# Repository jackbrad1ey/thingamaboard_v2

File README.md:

# Thingamaboard V2
This is the second iteration of my custom mechanical keyboard, a low-profile board aiming to be reliable, portable and fully-featured.

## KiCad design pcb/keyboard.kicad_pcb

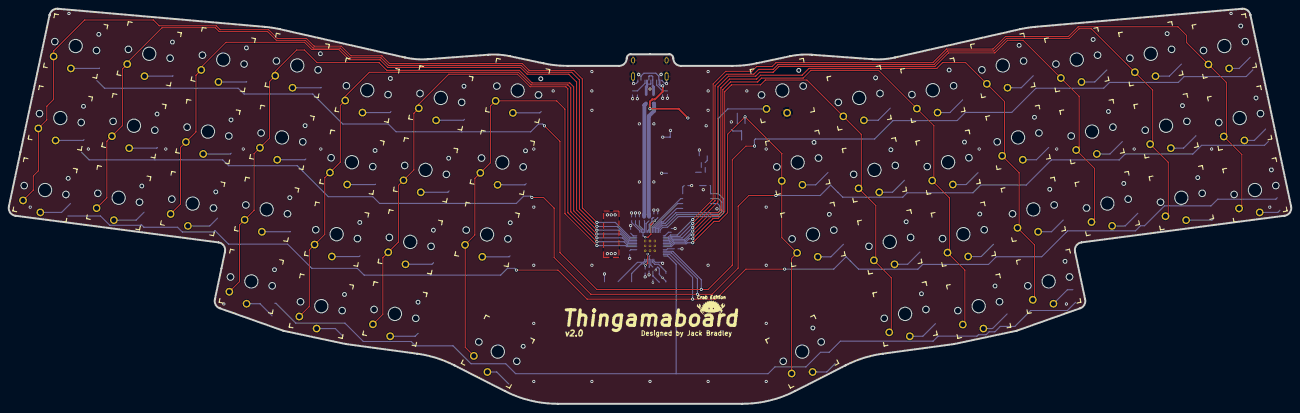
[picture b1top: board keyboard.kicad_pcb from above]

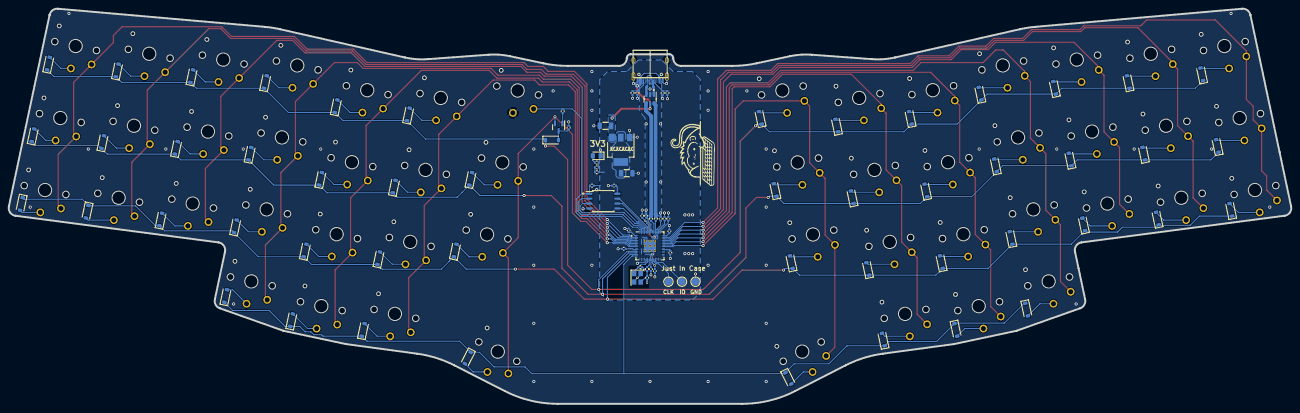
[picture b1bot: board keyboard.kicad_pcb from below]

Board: 2 copper layers, 331.1 x 102.0 mm, 140 parts (90 on the bottom side), 95 nets.

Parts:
C1, C16: 10u; C_1206_3216Metric
C2, C5, C6, C7, C10, C11, C12, C13, C14, C15: 100n; C_0402_1005Metric
C3, C4: 15p; C_0402_1005Metric
C8, C9: 1u; C_0402_1005Metric
D1: NCD0805; LED_0805_2012Metric_Pad1.15x1.40mm_HandSolder
D2, D3, D4, D5, D6, D7, D8, D9, D10, D11, D12, D13, D14, D15, D16, D17, D18, D19, D20, D21, D22, D23, D24, D25, D26, D27, D28, D29, D30, D31, D32, D33, D34, D35, D36, D37, D38, D39, D40, D41, D42, D43, D44, D45, D46, D47, D48, D49, D50, D51: D_Small; D_SOD-123
J1: USB_C_Receptacle_USB2.0; TYPE-C-31-M-12
Q1: S8550; SOT-23
R1, R2, R3, R12, R13: 27; R_0402_1005Metric
R4, R5, R6, R7, R8, R10: 10k; R_0402_1005Metric
R9, R11: 1k; R_0402_1005Metric
SW1, SW2, SW3, SW4, SW5, SW6, SW7, SW8, SW9, SW10, SW11, SW12, SW13, SW14, SW15, SW16, SW17, SW18, SW19, SW20, SW21, SW22, SW23, SW24, SW25, SW26, SW27, SW28, SW29, SW30, SW31, SW32, SW33, SW34, SW35, SW36, SW37, SW38, SW39, SW40, SW41, SW42, SW43, SW44, SW45, SW46, SW47, SW48, SW49, SW50: SW_Push; SW_PG1350
TP1, TP2, TP3: TestPoint; TestPoint_Pad_D2.0mm
U1: NCP1117-3.3_SOT223; SOT-223-3_TabPin2
U2: USBLC6-2SC6; SOT-23-6
U3: W25Q128JVS; SOIC-8_5.23x5.23mm_P1.27mm
U4: RP2040; QFN-56-1EP_7x7mm_P0.4mm_EP3.2x3.2mm
Y1: ABM8-272_T3; Crystal_SMD_3225-4Pin_3.2x2.5mm

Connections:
+1V1: C2.1, C6.1, C8.1, U4.23 (DVDD), U4.45 (VREG_VOUT), U4.50 (DVDD)
+3V3: C5.1, C7.1, C9.1, C10.1, C11.1, C12.1, C13.1, C14.1, C15.1, C16.1, R1.1, R8.1, U1.2 (VO), U3.8 (VCC), U4.1 (IOVDD), U4.10 (IOVDD), U4.22 (IOVDD), U4.26 (RUN), U4.33 (IOVDD), U4.42 (IOVDD), U4.43 (ADC_AVDD), U4.44 (VREG_IN), U4.48 (USB_VDD), U4.49 (IOVDD)
/MCU/BOOT: R8.2, R9.1, SW1.2, U3.1 (~CS), U4.56 (QSPI_SS)
/MCU/QSPI_SCLK: U3.6 (CLK), U4.52 (QSPI_SCLK)
/MCU/QSPI_SD0: U3.5 (DI(IO0)), U4.53 (QSPI_SD0)
/MCU/QSPI_SD1: U3.2 (DO(IO1)), U4.55 (QSPI_SD1)
/MCU/QSPI_SD2: U3.3 (IO2), U4.54 (QSPI_SD2)
/MCU/QSPI_SD3: U3.7 (IO3), U4.51 (QSPI_SD3)
/MCU/SWCLK: TP2.1, U4.24 (SWCLK)
/MCU/SWDIO: TP1.1, U4.25 (SWD)
/MCU/USB_D+: R12.1, U2.4 (I/O2)
/MCU/USB_D-: R13.1, U2.6 (I/O1)
/MCU/XIN: C3.1, U4.20 (XIN), Y1.1
/MCU/XOUT: R11.2, U4.21 (XOUT)
/MCU/col0: SW2.2, SW3.2, SW4.2, U4.41 (GPIO29_ADC3)
/MCU/col1: SW5.2, SW6.2, SW7.2, U4.40 (GPIO28_ADC2)
/MCU/col2: SW8.2, SW9.2, SW10.2, U4.39 (GPIO27_ADC1)
/MCU/col3: SW11.2, SW12.2, SW13.2, SW14.2, U4.38 (GPIO26_ADC0)
/MCU/col4: SW15.2, SW16.2, SW17.2, SW18.2, U4.37 (GPIO25)
/MCU/col5: SW19.2, SW20.2, SW21.2, SW22.2, U4.36 (GPIO24)
/MCU/col6: SW23.2, SW24.2, SW25.2, SW26.2, U4.35 (GPIO23)
/MCU/col7: Q1.2 (E), SW27.2, SW28.2, SW29.2, U4.8 (GPIO6)
/MCU/col8: SW30.2, SW31.2, SW32.2, SW33.2, U4.7 (GPIO5)
/MCU/col9: SW34.2, SW35.2, SW36.2, SW37.2, U4.6 (GPIO4)
/MCU/col10: SW38.2, SW39.2, SW40.2, SW41.2, U4.5 (GPIO3)
/MCU/col11: SW42.2, SW43.2, SW44.2, U4.4 (GPIO2)
/MCU/col12: SW45.2, SW46.2, SW47.2, U4.3 (GPIO1)
/MCU/col13: SW48.2, SW49.2, SW50.2, U4.2 (GPIO0)
/MCU/row0: D2.1 (K), D5.1 (K), D8.1 (K), D11.1 (K), D15.1 (K), D19.1 (K), D23.1 (K), D27.1 (K), D31.1 (K), D35.1 (K), D39.1 (K), D43.1 (K), D46.1 (K), D49.1 (K), U4.11 (GPIO8)
/MCU/row1: D3.1 (K), D6.1 (K), D9.1 (K), D12.1 (K), D16.1 (K), D20.1 (K), D24.1 (K), D28.1 (K), D32.1 (K), D36.1 (K), D40.1 (K), D44.1 (K), D47.1 (K), D50.1 (K), U4.12 (GPIO9)
/MCU/row2: D4.1 (K), D7.1 (K), D10.1 (K), D13.1 (K), D17.1 (K), D21.1 (K), D25.1 (K), D29.1 (K), D33.1 (K), D37.1 (K), D41.1 (K), D45.1 (K), D48.1 (K), D51.1 (K), U4.13 (GPIO10)
/MCU/row3: D14.1 (K), D18.1 (K), D22.1 (K), D26.1 (K), D30.1 (K), D34.1 (K), D38.1 (K), D42.1 (K), U4.14 (GPIO11)
/connectors/CC1: J1.A5 (CC1), R6.1, R7.1
/connectors/CC2: J1.B5 (CC2), R4.1, R5.1
/inputs/SS_OUT: D27.2 (A), Q1.3 (C), R10.1
GND: C1.2, C2.2, C3.2, C4.2, C5.2, C6.2, C7.2, C8.2, C9.2, C10.2, C11.2, C12.2, C13.2, C14.2, C15.2, C16.2, D1.1 (K), J1.A1 (GND), J1.A12 (GND), J1.B1 (GND), J1.B12 (GND), J1.S1 (SHIELD), R4.2, R5.2, R6.2, R7.2, R10.2, SW1.1, TP3.1, U1.1 (GND), U2.2 (GND), U3.4 (GND), U4.19 (TESTEN), U4.57 (GND), Y1.2, Y1.4
unnamed: C4.1, R11.1, Y1.3
unnamed: D1.2 (A), R3.2
unnamed: D2.2 (A), SW2.1
unnamed: D3.2 (A), SW3.1
unnamed: D4.2 (A), SW4.1
unnamed: D5.2 (A), SW5.1
unnamed: D6.2 (A), SW6.1
unnamed: D7.2 (A), SW7.1
unnamed: D8.2 (A), SW8.1
unnamed: D9.2 (A), SW9.1
unnamed: D10.2 (A), SW10.1
unnamed: D11.2 (A), SW11.1
unnamed: D12.2 (A), SW12.1
unnamed: D13.2 (A), SW13.1
unnamed: D14.2 (A), SW14.1
unnamed: D15.2 (A), SW15.1
unnamed: D16.2 (A), SW16.1
unnamed: D17.2 (A), SW17.1
unnamed: D18.2 (A), SW18.1
unnamed: D19.2 (A), SW19.1
unnamed: D20.2 (A), SW20.1
unnamed: D21.2 (A), SW21.1
unnamed: D22.2 (A), SW22.1
unnamed: D23.2 (A), SW23.1
unnamed: D24.2 (A), SW24.1
unnamed: D25.2 (A), SW25.1
unnamed: D26.2 (A), SW26.1
unnamed: D28.2 (A), SW27.1
unnamed: D29.2 (A), SW28.1
unnamed: D30.2 (A), SW29.1
unnamed: D31.2 (A), SW30.1
unnamed: D32.2 (A), SW31.1
unnamed: D33.2 (A), SW32.1
unnamed: D34.2 (A), SW33.1
unnamed: D35.2 (A), SW34.1
unnamed: D36.2 (A), SW35.1
unnamed: D37.2 (A), SW36.1
unnamed: D38.2 (A), SW37.1
unnamed: D39.2 (A), SW38.1
unnamed: D40.2 (A), SW39.1
unnamed: D41.2 (A), SW40.1
unnamed: D42.2 (A), SW41.1
unnamed: D43.2 (A), SW42.1
unnamed: D44.2 (A), SW43.1
unnamed: D45.2 (A), SW44.1
unnamed: D46.2 (A), SW45.1
unnamed: D47.2 (A), SW46.1
unnamed: D48.2 (A), SW47.1
unnamed: D49.2 (A), SW48.1
unnamed: D50.2 (A), SW49.1
unnamed: D51.2 (A), SW50.1
unnamed: J1.A6 (D+), J1.B6 (D+), U2.3 (I/O2)
unnamed: J1.A7 (D-), J1.B7 (D-), U2.1 (I/O1)
unnamed: Q1.1 (B), R9.2
unnamed: R1.2, R2.1
unnamed: R2.2, R3.1
unnamed: R13.2, U4.46 (USB_DM)
unnamed: R12.2, U4.47 (USB_DP)
VBUS: C1.1, J1.A4 (VBUS), J1.A9 (VBUS), J1.B4 (VBUS), J1.B9 (VBUS), U1.3 (VI), U2.5 (VBUS)

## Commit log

2024-09-03 Lot's of work has been done
2024-09-04 Preliminary layout done
2024-09-06 Haven't backed up in a bit
2024-09-07 Preliminary case design done, moving on to PCB design
2024-09-07 PCB work in progress
2024-09-07 Schematic done, starting PCB design
2024-09-07 Switches placement done, updated footprints to include model
2024-09-07 Starting diode placement
2024-09-07 Diode placement done
2024-09-07 Routing in progress
2024-09-08 More routing progress
2024-09-08 Further progress on routing
2024-09-08 More routing yippieeeee
2024-09-09 Preliminary routing done
2024-09-09 PCB updates, cad updates
2024-09-11 Ready to produce test production files before updating some components
2024-09-11 Rerouted a lot of stuff
2024-09-11 Further updates to routing
2024-09-12 PCB design complete
2024-09-13 Touched up PCB slightly
2024-09-14 PCB ready for production
2024-09-14 Updated assembly a little
2024-09-15 Updates to the CAD
2024-09-18 Updated case outline for countersunk bolts
2024-09-19 Working on the new keyboard CAD
2024-09-24 Starting some work on the code
2024-09-29 Working on firmware implementation
2024-09-29 Working example HID code
2024-10-02 Key scanning code ready for testing
2024-10-05 CAD ready for JLC review
2024-10-20 Firmware in progress
2024-10-21 Updated layout further
2025-01-03 Minor changes to keymap
2025-01-03 Added README
